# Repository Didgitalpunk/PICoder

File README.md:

# PICoder
repository for an encoder circuit meant to replace the HCTL2020 and its brothers with a dsPIC33 uC outputing the data over serial, as well as an extra RX pin meant, for example, for a Sabertooth motor controller.

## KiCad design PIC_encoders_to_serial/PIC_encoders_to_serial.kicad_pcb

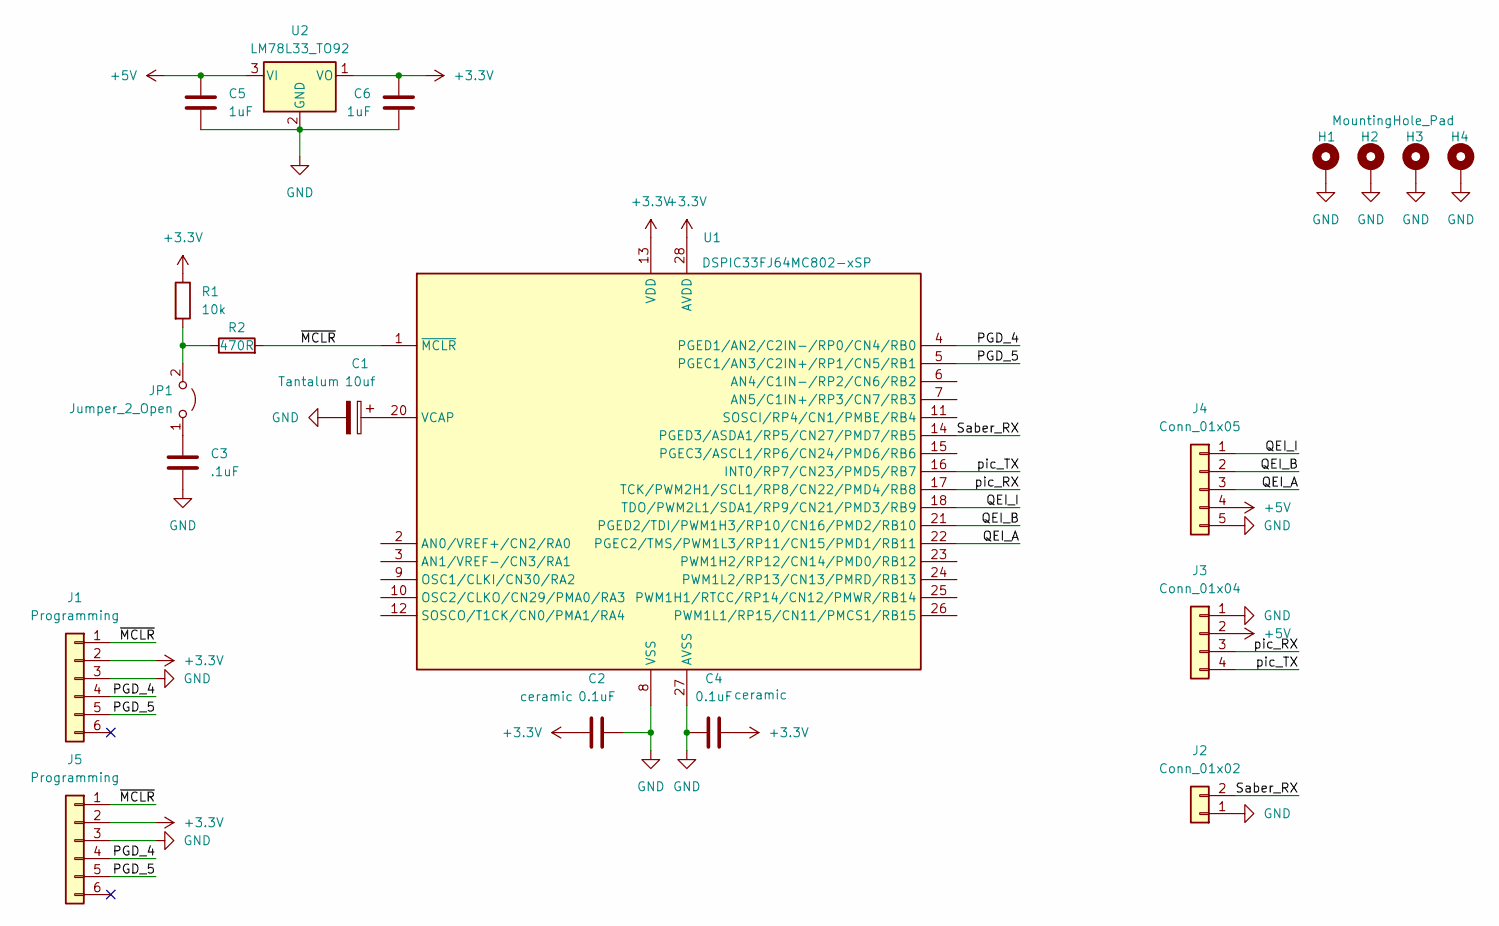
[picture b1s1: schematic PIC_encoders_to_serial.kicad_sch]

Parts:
C1: 10uf; CP_EIA-1608-08_AVX-J
C2, C4: 0.1uF; C_0402_1005Metric
C3: .1uF; C_0402_1005Metric
C5, C6: 1uF; C_0402_1005Metric
H1, H2, H3, H4: MountingHole_Pad; MountingHole_3.2mm_M3_Pad_Via
J1: Programming; Tag-Connect_TC2030-IDC-NL_2x03_P1.27mm_Vertical_NO-KEEPOUT_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
J2: Conn_01x02; Molex_SPOX_5268-02A_1x02_P2.50mm_Horizontal
J3: Conn_01x04; Molex_SPOX_5268-04A_1x04_P2.50mm_Horizontal
J4: Conn_01x05; Molex_SPOX_5268-05A_1x05_P2.50mm_Horizontal
J5: Programming; PinHeader_1x06_P2.54mm_Vertical
JP1: Jumper_2_Open; SolderJumper-2_P1.3mm_Open_RoundedPad1.0x1.5mm
R1: 10k; R_0402_1005Metric
R2: 470R; R_0402_1005Metric
U1: DSPIC33FJ64MC802-xSP; DIP-28_W7.62mm
U2: LM78L33_TO92; TO-92_Inline

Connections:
+3.3V: C2.1, C4.2, C6.1, J1.2, J5.2, R1.1, U1.13 (VDD), U1.28 (AVDD), U2.1 (VO)
+5V: C5.1, J3.2, J4.4, U2.3 (VI)
/PGD_4: J1.4, J5.4, U1.4 (PGED1/AN2/C2IN-/RP0/CN4/RB0)
/PGD_5: J1.5, J5.5, U1.5 (PGEC1/AN3/C2IN+/RP1/CN5/RB1)
/QEI_A: J4.3, U1.22 (PGEC2/TMS/PWM1L3/RP11/CN15/PMD1/RB11)
/QEI_B: J4.2, U1.21 (PGED2/TDI/PWM1H3/RP10/CN16/PMD2/RB10)
/QEI_I: J4.1, U1.18 (TDO/PWM2L1/SDA1/RP9/CN21/PMD3/RB9)
/Saber_RX: J2.2, U1.14 (PGED3/ASDA1/RP5/CN27/PMD7/RB5)
/pic_RX: J3.3, U1.17 (TCK/PWM2H1/SCL1/RP8/CN22/PMD4/RB8)
/pic_TX: J3.4, U1.16 (INT0/RP7/CN23/PMD5/RB7)
/~MCLR: J1.1, J5.1, R2.2, U1.1 (~MCLR)
GND: C1.2, C2.2, C3.2, C4.1, C5.2, C6.2, H1.1, H2.1, H3.1, H4.1, J1.3, J2.1, J3.1, J4.5, J5.3, U1.8 (VSS), U1.19 (VSS), U1.27 (AVSS), U2.2 (GND)
unnamed: C3.1, JP1.1 (A)
unnamed: JP1.2 (B), R1.2, R2.1
unnamed: C1.1, U1.20 (VCAP)

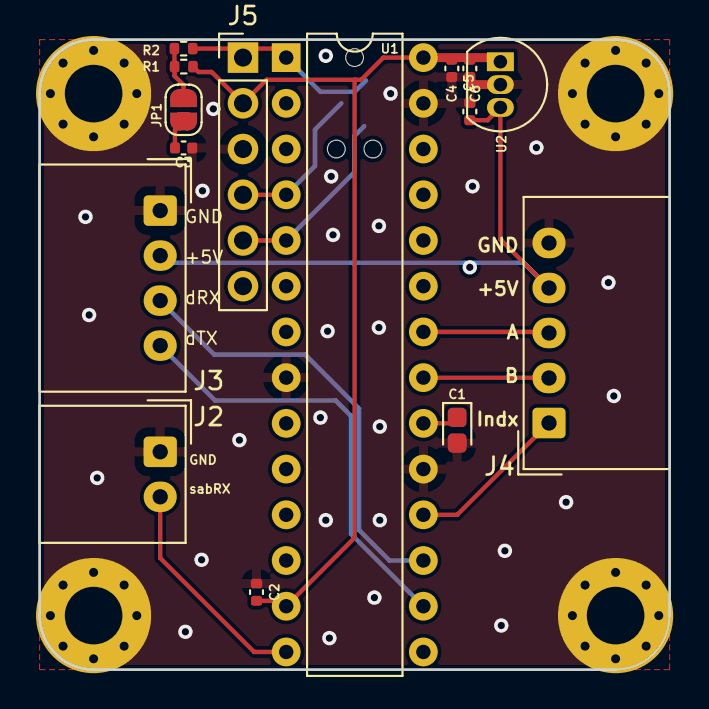
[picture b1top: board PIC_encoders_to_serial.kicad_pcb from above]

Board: 2 copper layers, 35.0 x 35.0 mm, 20 parts (1 on the bottom side), 15 nets.

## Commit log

2024-09-25 initial commit
    added initial work:
    - 35x35mm pcb, 2mm thick for rigidity (for now), with M3 mounting holes,
    - JST XH connectors for encoder input, serial, and sabertooth output, all going to 5V compliant pins on the dsPIC
    - both a tag-connect and a normal header interface for programming
    - for now, DSPIC33FJ64MC802-xSP
    - for now, TO92 packaged LM78L33 voltage regulator to bring 5v to 3.3v for the dsPIC
2024-09-25 changed connectors from JST XH to Molex mini-SPOX
    mini-spox is smaller, but retains an almost 2.54mm pitch, so is still somewhat compatible with pin headers if need be
2025-03-05 Added motor control flowchart.drawio
2025-03-14 Update README.md
    spelling
